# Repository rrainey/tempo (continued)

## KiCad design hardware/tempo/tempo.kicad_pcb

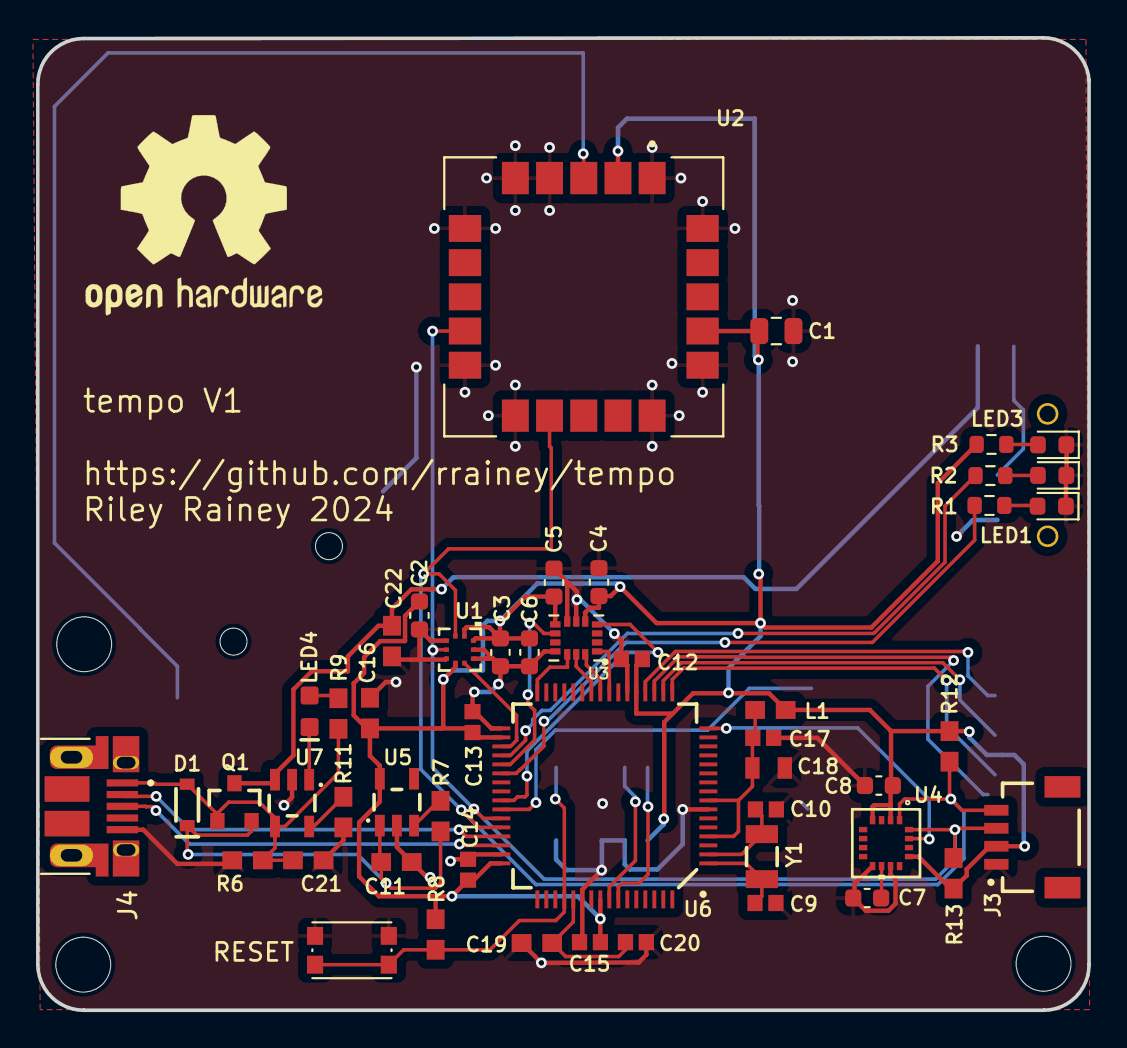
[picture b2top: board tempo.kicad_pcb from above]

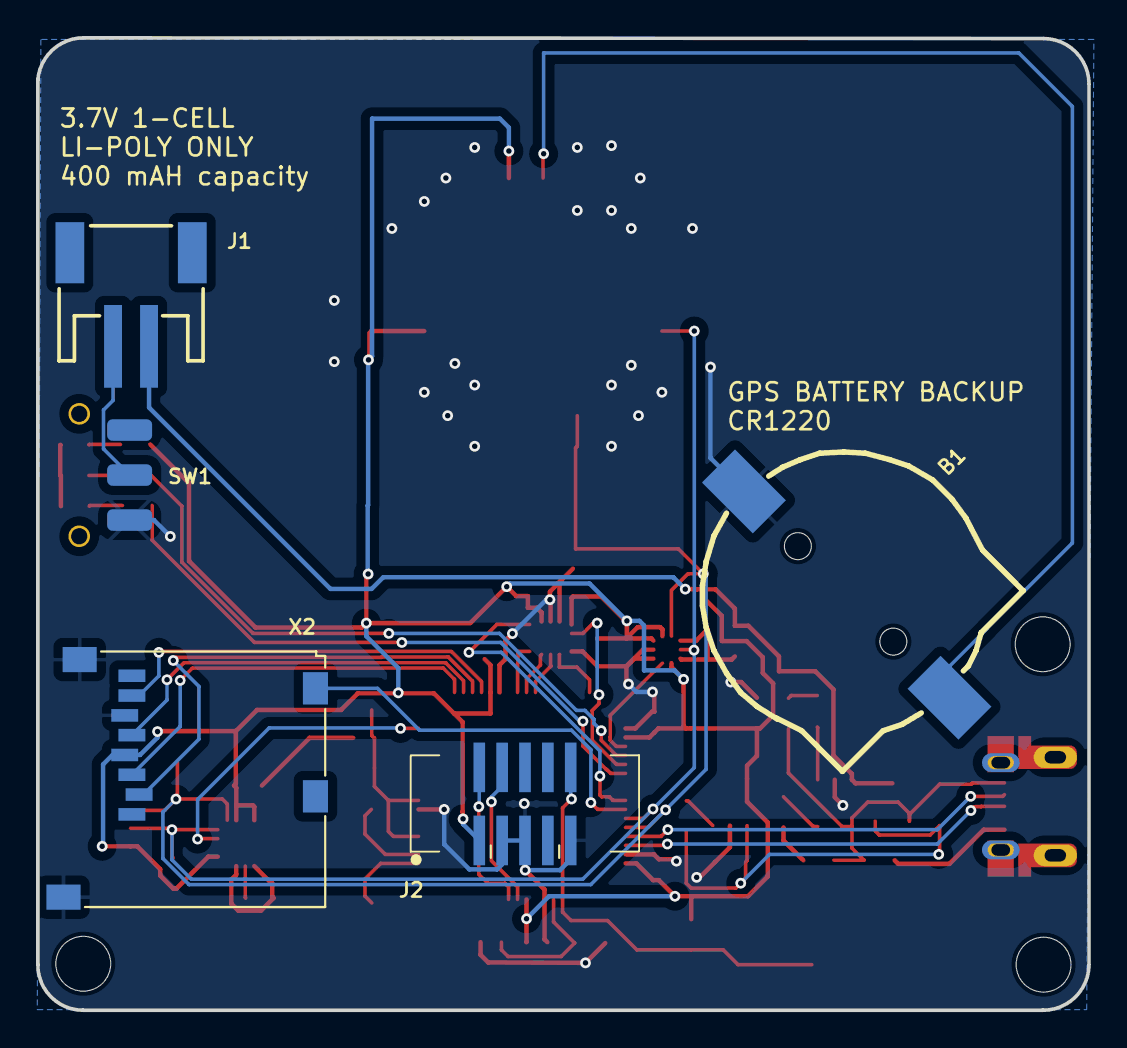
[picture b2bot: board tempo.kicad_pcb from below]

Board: 2 copper layers, 58.4 x 54.0 mm, 60 parts (5 on the bottom side), 41 nets.

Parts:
B1: CR1220; CR1220-2
C1: 10uF; C_0805_2012Metric
C2, C3: 100nF; C_0603_1608Metric
C4: 0.1uF; C_0603_1608Metric
C5: 10nF; C_0603_1608Metric
C6: 2.2uF; C_0603_1608Metric
C7, C8: 10uF; C_0603_1608Metric
C9, C10: 15PF-0402-50V-5%; 0402
C11: 1.0UF-0603-16V-10%-X7R; 0603
C12, C13, C14, C15, C17, C20: 0.1UF-0402-16V-10%; 0402
C16: 2.2UF-0603-10V-20%; 0603
C18: 10UF-0805-10V-10%; 0805
C19, C21, C22: 4.7UF-0603-6.3V-(10%); 0603
D1: 1A/23V/620mV; SOD-323
FRAME1: FRAME-LETTER; CREATIVE_COMMONS
H1, H2, H3: STAND-OFFTIGHT; STAND-OFF-TIGHT
J1: JSTPH; JSTPH2
J2: 3221-10-0300-00-TR
J3: QWIIC_CONNECTORJS-1MM; JST04_1MM_RA
J4: 10103594-0001LF; AMPHENOL_10103594-0001LF
L1: 220 Ω FERRITE; 0603
LED1, LED3: LTST-S270KGKT; LED_0603_1608Metric
LED2: LTST-S270KRKT; LED_0603_1608Metric
LED4: Yellow; LED-0603
LOGO2: OSHW-LOGOS; OSHW-Logo2_14.6x12mm_SilkScreen
Q1: DMP3125L; SOT23-3@1
R1, R2, R3: 2.2K; R_0603_1608Metric
R6, R7, R8: 10KOHM-0603-1/10W-1%; 0603
R9: 1K; 0603
R11: 2.0k; 0603
R12, R13: 2.2KOHM-0603-1/10W-1%; 0603
S1: RESET; SW_Push_1P1T_NO_CK_KMR2
SW1: JS102011SAQN
U1: BMP390; LGA10_BMP390_BOS
U2: SAM-M10Q; MODULE_SAM-M8Q-0-10
U3: ICM-42688-V; PQFN50P300X250X97-14N
U4: MMC5983MA; MMC5983MA_MEM
U5: SPX3819M5-L-3-3/TR; SOT23-5
U6: ATSAMD51J20A-A; TQFP64
U7: MCP73831; SOT23-5
X2: MEM2061-01-188-00-A; MICROSD
Y1: 32.768kHz; CRYSTAL-SMD-3.2X1.5MM

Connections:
3.3V: C1.1, C2.1, C3.1, C4.1, C5.1, C6.1, C8.1, C12.1, C13.1, C14.1, C15.1, C16.1, J2.1, J3.2, L1.1, R3.1, R8.2, R12.2, R13.2, U1.1 (VDDIO), U1.6 (CSB), U1.10 (VDD), U2.2 (VCC_IO), U2.17 (VCC), U3.5 (VDDIO), U3.8 (VDD), U4.2 (VDD), U4.4 (SPI_CS), U4.13 (VDDIO), U5.5 (OUT), U6.21 (VDDIO0), U6.34 (VDDIO1), U6.48 (VDDIO2), U6.56 (VDDIO3), X2.4 (SD_VDD)
/D5: U3.12 (AP_CS), U6.32 (PA15)
/D6: U3.4 (INT1/INT), U6.41 (PA20)
/D7: U6.42 (PA21), X2.CD1 (CARD_DETECT)
/D9: U4.15 (INT), U6.16 (PA07)
/D10: U3.9 (INT2/FSYNC/CLKIN), U6.37 (PA18)
/D11: U1.7 (INT), U6.35 (PA16)
/D12: R1.1, U6.38 (PA19)
/D13: R2.1, U6.36 (PA17)
/D+: J4.3 (D+), U6.46 (PA25)
/D-: J4.2 (D-), U6.45 (PA24)
/EN: R7.1, U5.3 (EN)
/FLASH_CS: U6.19 (PA10), X2.2 (CS)
/FLASH_MISO: U6.20 (PA11), X2.7 (DATA_OUT)
/FLASH_MOSI: U6.17 (PA08), X2.3 (DATA_IN)
/FLASH_SCK: U6.18 (PA09), X2.5 (SCLK)
/MISO: U3.1 (AP_SDO/AP_AD0), U6.24 (PB11)
/MOSI: U3.14 (AP_SDA/AP_SDIO/AP_SDI), U6.25 (PB12)
/SCK: U3.13 (AP_SCL/AP_SCLK), U6.26 (PB13)
/SCL: J3.4, R12.1, U1.2 (SCK), U2.12 (SCL), U4.1 (SCL/SPI_SCK), U6.44 (PA23)
/SDA: J3.3, R13.1, U1.4 (SDI), U2.9 (SDA), U4.16 (SDA/SPI_SDI), U6.43 (PA22)
/SWDCLK: J2.4, U6.57 (PA30)
/SWDIO: J2.2, U6.58 (PA31)
/VBACKUP: B1.+, U2.3 (V_BCKP)
/XIN32: C9.1, U6.1 (PA00), Y1.P$1 (1)
/XOUT32: C10.1, U6.2 (PA01), Y1.P$2 (2)
/~RESET: J2.10, R8.1, S1.2, U6.52 (~RESET)
GND: B1.-, C1.2, C2.2, C3.2, C4.2, C5.2, C6.2, C7.2, C8.2, C9.2, C10.2, C11.2, C12.2, C13.2, C14.2, C15.2, C16.2, C17.2, C18.2, C19.2, C20.2, C21.2, C22.2, J2.3, J2.5, J2.9, J3.1, J4.5 (GND), LED1.1 (K), LED2.1 (K), LED3.1 (K), R6.1, R11.1, S1.1, SW1.3 (C), U1.3 (VSS), U1.5 (SDO), U1.8 (VSS), U1.9 (VSS), U2.1 (GND), U2.4 (GND), U2.5 (GND), U2.6 (GND), U2.10 (GND), U2.11 (GND), U2.15 (GND), U2.16 (GND), U2.20 (GND), U3.6 (GND), U3.7 (RESV_7), U3.11 (RESV_11), U4.9 (GND), U4.11 (GND), U5.2 (GND), U6.7 (GND0), U6.22 (GND1), U6.33 (GND2), U6.47 (GND3), U6.54 (GND4), U7.2 (VSS), X2.6 (GND@3), X2.MT1 (GND@2), X2.MT2 (GND@1)
unnamed: LED1.2 (A), R1.2
unnamed: LED2.2 (A), R2.2
unnamed: LED3.2 (A), R3.2
unnamed: LED4.A, R9.2
unnamed: J1.1, SW1.2 (B)
unnamed: C7.1, U4.10 (CAP)
unnamed: R11.2, U7.5 (PROG)
unnamed: LED4.C, U7.1 (STAT)
VCC: C19.1, C20.1, U6.53 (VDDCORE)
VDDA: C17.1, C18.1, L1.2, U6.4 (PA03), U6.8 (VDDANA)
VIN: C11.1, D1.C, Q1.2 (S), R7.2, U5.1 (IN)
V_BATT: C22.1, J1.2, Q1.3 (D), U7.3 (VBAT)
V_USB: C21.1, D1.A, J4.1 (VCC), Q1.1 (G), R6.2, R9.1, U7.4 (VIN)

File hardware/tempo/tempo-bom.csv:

Source:,C:\Users\rrain\OneDrive\Documents\GitHub\SAMD51_Thing_Plus\peakick\peakick.kicad_sch,,,,,,,,,,,,,,
Date:,2/8/2024 16:50,,,,,,,,,,,,,,
Tool:,Eeschema 7.0.5,,,,,,,,,,,,,,
Generator:,C:\Program Files\KiCad\7.0\bin\scripting\plugins/bom_csv_grouped_by_value.py,,,,,,,,,,,,,,
Component Count:,55,,,,,,,,,,,,,,
,,,,,,,,,,,,,,,
Collated Components:,,,,,,,,,,,,,,,
,,,,,,,,,,,,,,,
Item,Qty,Reference(s),Value,LibPart,Footprint,Datasheet,DNP,MANUFACTURER,MAXIMUM_PACKAGE_HEIGHT,MPN,NOTES,PACKAGE,PARTREV,PROD_ID,STANDARD
1,1,B1,CR1220,peakick:BATTERYCR1220_2,peakick:CR1220-2,https://www.keyelco.com/userAssets/file/M65p2.pdf,,Keystone,,1056TR,BATT HOLDER,,,,
2,1,C1,10uF,Device:C,Capacitor_SMD:C_0805_2012Metric,~,,,,,,0805,,,
3,2,"C2, C3",100nF,Device:C_Small,Capacitor_SMD:C_0603_1608Metric,~,,,,,X7R,0603,,,
4,1,C4,0.1uF,Device:C_Small,Capacitor_SMD:C_0603_1608Metric,~,,,,,X7R,0603,,,
5,1,C5,10nF,Device:C_Small,Capacitor_SMD:C_0603_1608Metric,~,,,,,X7R,0603,,,
6,1,C6,2.2uF,Device:C_Small,Capacitor_SMD:C_0603_1608Metric,~,,,,,X7R,0603,,,
7,2,"C7, C8",10uF,Device:C_Small,Capacitor_SMD:C_0603_1608Metric,~,,,,,X7R,0603,,,
8,2,"C9, C10",15PF-0402-50V-5%,SAMD51_Thing_Plus-eagle-import:15PF-0402-50V-5%,0402,,,,,,,0402,,,
9,1,C11,1.0UF-0603-16V-10%-X7R,SAMD51_Thing_Plus-eagle-import:1.0UF-0603-16V-10%-X7R,0603,,,,,,,0603,,,
10,6,"C12, C13, C14, C15, C17, C20",0.1UF-0402-16V-10%,SAMD51_Thing_Plus-eagle-import:0.1UF-0402-16V-10%,0402,,,,,,,0402,,,
11,1,C16,2.2UF-0603-10V-20%,SAMD51_Thing_Plus-eagle-import:2.2UF-0603-10V-20%,0603,,,,,,,0603,,,
12,1,C18,10UF-0805-10V-10%,SAMD51_Thing_Plus-eagle-import:10UF-0805-10V-10%,0805,,,,,,,0805,,,
13,3,"C19, C21, C22",4.7UF-0603-6.3V-(10%),SAMD51_Thing_Plus-eagle-import:4.7UF-0603-6.3V-(10%),0603,,,,,,,0603,,,
14,1,D1,1A/23V/620mV,SAMD51_Thing_Plus-eagle-import:DIODE-SCHOTTKY-BAT20J,SOD-323,,,,,,,SOD-323,,,
15,1,J1,JSTPH,Adafruit Feather M0 Adalogger-eagle-import:CON_JST_PH_2PIN,JSTPH2,,,JST,5.5mm,S2B-PH-SM4-TB,,,,,
16,1,J2,3221-10-0300-00-TR,20021221:20021221-00010C4LF,peakick:3221-10-0300-00-TR,https://media.digikey.com/pdf/Data%20Sheets/CNC%20Tech%20PDF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,,,,3221-10-0300-00-TR,,,,,
17,1,J3,QWIIC_CONNECTORJS-1MM,SAMD51_Thing_Plus-eagle-import:QWIIC_CONNECTORJS-1MM,JST04_1MM_RA,,DNP,JST,,SM04B-SRSS-TB,do not place,,,,
18,1,J4,AMP FCI 10103594-0001LF,SAMD51_Thing_Plus-eagle-import:USB_MICRO-B_HALF_PTH_MILL,USB-MICROB-PTH-MILL,,,,,,,,,,
19,1,L1,220 Ω FERRITE,SAMD51_Thing_Plus-eagle-import:INDUCTORFB-30OHM,0603,,,MURATA,,BLM18RK221SN1D,see DS60001507E-page 2098,,,NDUC-07859,
20,2,"LED1, LED3",LTST-S270KGKT,Device:LED,LED_SMD:LED_0603_1608Metric,~,,Lite-On,,LTST-S270KGKT,GREEN LED,,,,
21,1,LED2,LTST-S270KRKT,Device:LED,LED_SMD:LED_0603_1608Metric,~,,Lite-On,,LTST-S270KRKT,RED LED,,,,
22,1,LED4,Yellow,SAMD51_Thing_Plus-eagle-import:LED-YELLOW0603,LED-0603,,,Lite-On,,LTST-S270YKT,YELLOW LED,,,,
23,1,Q1,DMP3125L,SAMD51_Thing_Plus-eagle-import:MOSFET-PCHANNELDMG2307L,SOT23-3@1,https://www.diodes.com/assets/Datasheets/DMP3125L.pdf,,Diodes Incorporated,,DMP3125L,DMP3125L or DMG2307L,SOT23,,,
24,3,"R1, R2, R3",2.2K,Adafruit MPU6050-eagle-import:RESISTOR_0603_NOOUT,Resistor_SMD:R_0603_1608Metric,,,,,,10%,0603,,,
25,3,"R6, R7, R8",10KOHM-0603-1/10W-1%,SAMD51_Thing_Plus-eagle-import:10KOHM-0603-1/10W-1%,0603,,,,,,,0603,,,
26,1,R9,1K,SAMD51_Thing_Plus-eagle-import:1KOHM-1/10W-1%(0603),0603,,,,,,,0603,,,
27,1,R11,2.0k,SAMD51_Thing_Plus-eagle-import:2.0KOHM1/10W5%(0603),0603,,,,,,,0603,,,
28,2,"R12, R13",2.2KOHM-0603-1/10W-1%,SAMD51_Thing_Plus-eagle-import:2.2KOHM-0603-1/10W-1%,0603,,,,,,,0603,,,
29,1,S1,RESET,peakick:KMR2_TACTILE_SWITCH,Button_Switch_SMD:SW_Push_1P1T_NO_CK_KMR2,https://www.ckswitches.com/media/1479/kmr2.pdf,,CK Switches,,KMR221 LFS,,,,,
30,1,SW1,JS102011SAQN,Switch:SW_SPDT,peakick:JS102011SAQN,https://www.ckswitches.com/media/1422/js.pdf,,CK Switches,,JS102011SAQN,,,,,
31,1,U1,BMP390,peakick:BMP390,LGA10_BMP390_BOS,BMP390,,Bosch Sensortec,,BMP390,,LGA-10,,,
32,1,U2,SAM-M10Q,dropkick:SAM-M8Q-0-10,MODULE_SAM-M8Q-0-10,https://content.u-blox.com/sites/default/files/documents/SAM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,,u-blox,6.80mm,SAM-M10Q-00B,GNSS RECEIVER,,R07,,Manufacturer Recommendations
33,1,U3,ICM-42688-V,dropkick:ICM-42688-P,peakick:PQFN50P300X250X97-14N,,,TDK InvenSense,0.97mm,ICM-42688-V,,LGA-14,1.2,,IPC-7351B
34,1,U4,MMC5983MA,peakick:MMC5983MA,MMC5983MA_MEM,https://www.mouser.com/datasheet/2/821/Memsic_09102019_MMC59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,,,1.0mm,MMC5983MA,,LGA-16,,,
35,1,U5,SPX3819M5-L-3-3/TR,SAMD51_Thing_Plus-eagle-import:V_REG_LDOSMD,SOT23-5,,,Maxlinear,,SPX3819M5-L-3-3/TR,,,,VREG-12457,
36,1,U6,ATSAMD51J20A-A,SAMD51_Thing_Plus-eagle-import:ATSAMD51J20A-A,TQFP64,,,Microchip,,ATSAMD51J20A-AUT,,,,,
37,1,U7,MCP73831,SAMD51_Thing_Plus-eagle-import:MCP73831,SOT23-5,,,Microchip,,MCP73831T-4ADI/OT,,,,,
38,1,X2,MEM2061-01-188-00-A,Adafruit Feather M0 Adalogger-eagle-import:MICROSD,MICROSD,https://gct.co/files/specs/mem2061-spec.pdf,,GCT,,MEM2061-01-188-00-A,,,,,
39,1,Y1,32.768kHz,SAMD51_Thing_Plus-eagle-import:CRYSTAL-32.768KHZSMD-3.2X1.5,CRYSTAL-SMD-3.2X1.5MM,https://www.mouser.com/datasheet/2/137/FC_255_en-1649561.pdf,,SEIKO EPSON,,FC-135 32.7680KA-A5,,,,,

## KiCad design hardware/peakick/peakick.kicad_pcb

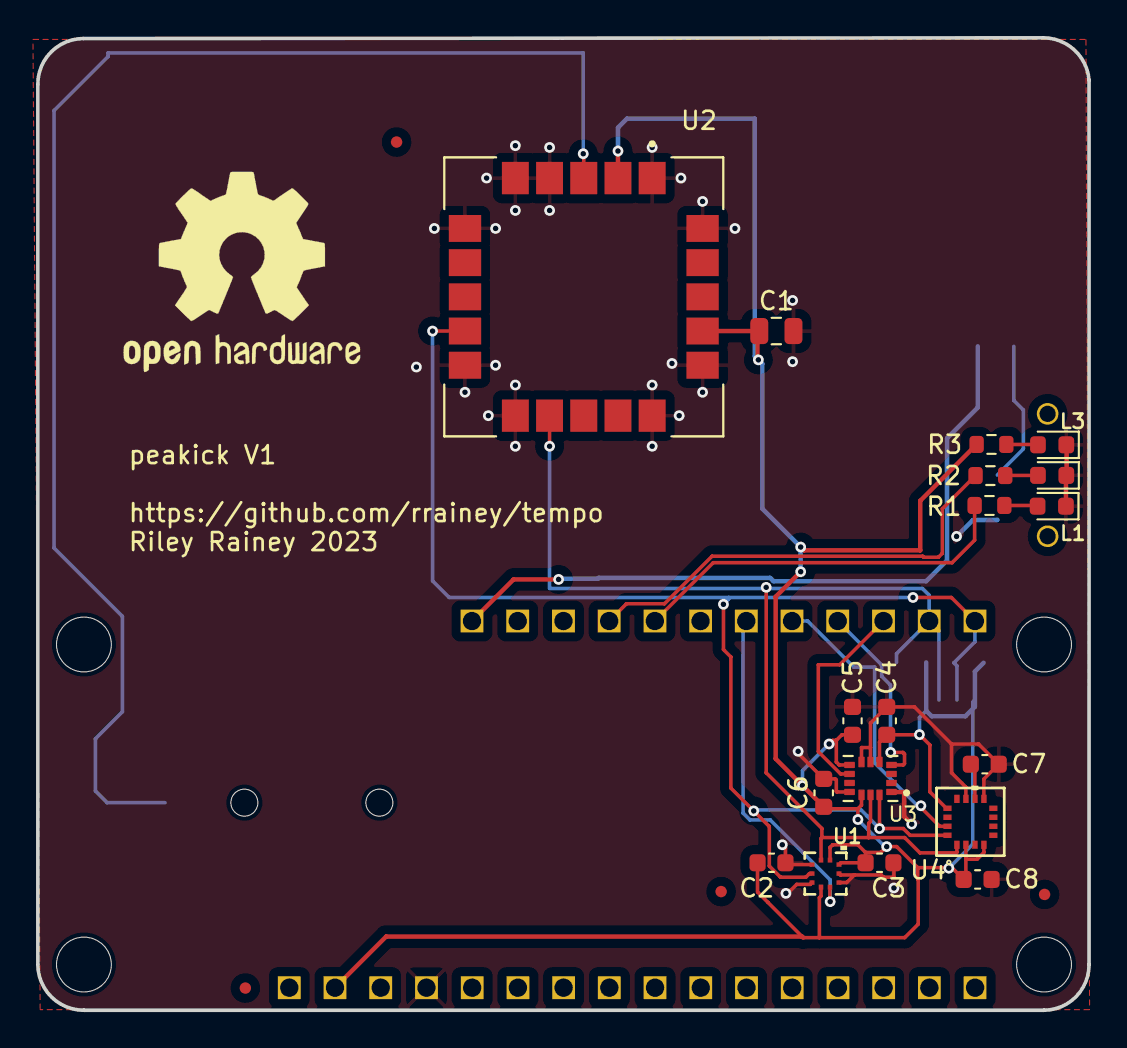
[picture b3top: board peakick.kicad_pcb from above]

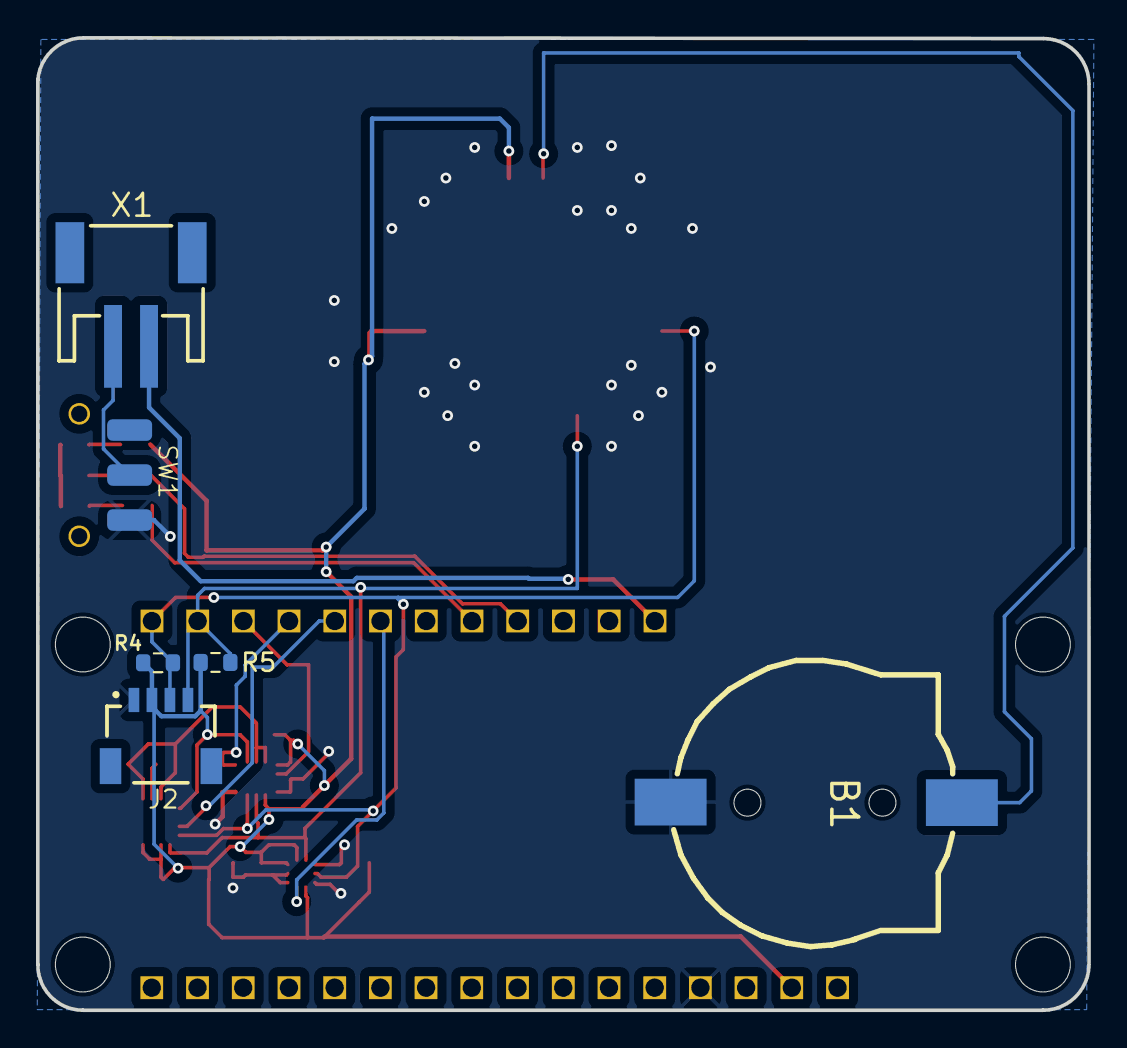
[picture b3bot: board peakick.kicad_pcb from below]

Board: 2 copper layers, 58.4 x 54.0 mm, 36 parts (6 on the bottom side), 17 nets.

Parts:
B1: CR1220; CR1220-2
C1: 10uF; C_0805_2012Metric
C2, C3: 100nF; C_0603_1608Metric
C4: 0.1uF; C_0603_1608Metric
C5: 10nF; C_0603_1608Metric
C6: 2.2uF; C_0603_1608Metric
C7, C8: 10uF; C_0603_1608Metric
FD1, FD2, FD3, FD4: FIDUCIALUFIDUCIAL; FIDUCIAL-MICRO
FRAME1: FRAME-LETTER; CREATIVE_COMMONS
H1, H2, H3, H4: STAND-OFFTIGHT; STAND-OFF-TIGHT
J1: CONN_161X16_SM_SQ_NOSILK; 1X16_SM_SQ_NOSILK
J2: QWIIC_RA; JST04_1MM_RA
J3: CONN_12SM_SQ_NO_SILK; 1X12_SM_SQ_NOSILK
L1, L3: LTST-S270KGKT; LED_0603_1608Metric
L2: LTST-S270KRKT; LED_0603_1608Metric
LOGO2: OSHW-LOGOS; OSHW-Logo2_14.6x12mm_SilkScreen
R1, R2, R3: 2.2K; R_0603_1608Metric
R4, R5: DNP; R_0603_1608Metric
SW1: JS102011SAQN
U1: BMP390; LGA10_BMP390_BOS
U2: SAM-M10Q; MODULE_SAM-M8Q-0-10
U3: ICM-42688-P; PQFN50P300X250X97-14N
U4: MMC5983MA; MMC5983MA_MEM
X1: JSTPH; JSTPH2

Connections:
3.3V: C1.1, C2.1, C3.1, C4.1, C5.1, C6.1, C8.1, J1.15, J2.2, R3.1, R4.1, R5.1, U1.1 (VDDIO), U1.6 (CSB), U1.10 (VDD), U2.2 (VCC_IO), U2.17 (VCC), U3.5 (VDDIO), U3.8 (VDD), U3.12 (AP_CS), U4.2 (VDD), U4.4 (SPI_CS), U4.13 (VDDIO)
/D4: J3.3, U3.9 (INT2/FSYNC/CLKIN)
/D6: J3.4, U3.4 (INT1/INT)
/D8: J3.5, U4.15 (INT)
/D10: J3.6, U1.7 (INT)
/D12: J3.8, R1.1
/D13: J3.9, R2.1
/SCL: J2.4, J3.2, R5.2, U1.2 (SCK), U2.12 (SCL), U3.13 (AP_SCL/AP_SCLK), U4.1 (SCL/SPI_SCK)
/SDA: J2.3, J3.1, R4.2, U1.4 (SDI), U2.9 (SDA), U3.14 (AP_SDA/AP_SDIO/AP_SDI), U4.16 (SDA/SPI_SDI)
/VBACKUP: B1.+, U2.3 (V_BCKP)
GND: B1.-, C1.2, C2.2, C3.2, C4.2, C5.2, C6.2, C7.2, C8.2, J1.13, J2.1, L1.1 (K), L2.1 (K), L3.1 (K), SW1.3 (C), U1.3 (VSS), U1.5 (SDO), U1.8 (VSS), U1.9 (VSS), U2.1 (GND), U2.4 (GND), U2.5 (GND), U2.6 (GND), U2.10 (GND), U2.11 (GND), U2.15 (GND), U2.16 (GND), U2.20 (GND), U3.1 (AP_SDO/AP_AD0), U3.6 (GND), U3.7 (RESV_7), U3.11 (RESV_11), U4.9 (GND), U4.11 (GND)
unnamed: L1.2 (A), R1.2
unnamed: L2.2 (A), R2.2
unnamed: L3.2 (A), R3.2
unnamed: SW1.2 (B), X1.1
unnamed: C7.1, U4.10 (CAP)
V_BATT: J3.12, X1.2

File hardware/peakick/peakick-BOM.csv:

"Source:","C:\Users\rrain\OneDrive\Documents\GitHub\tempo\hardware\peakick\peakick.kicad_sch"
"Date:","12/18/2023 11:48:49 AM"
"Tool:","Eeschema 7.0.5"
"Generator:","C:\Program Files\KiCad\7.0\bin\scripting\plugins/bom_csv_grouped_by_value.py"
"Component Count:","26"

"Collated Components:"

"Item","Qty","Reference(s)","Value","LibPart","Footprint","Datasheet","DNP","MANUFACTURER","MAXIMUM_PACKAGE_HEIGHT","MPN","Manufacturer Part","NOTES","PACKAGE","PARTREV","STANDARD"
"1","1","B1","CR1220","peakick:BATTERYCR1220_2","peakick:CR1220-2","https://www.keyelco.com/userAssets/file/M65p2.pdf","","Keystone","","1056TR","","BATT HOLDER","","",""
"2","1","C1","10uF","Device:C","Capacitor_SMD:C_0805_2012Metric","~","","","","","","","0805","",""
"3","2","C2, C3","100nF","Device:C_Small","Capacitor_SMD:C_0603_1608Metric","~","","","","","","X7R","0603","",""
"4","1","C4","0.1uF","Device:C_Small","Capacitor_SMD:C_0603_1608Metric","~","","","","","","X7R","0603","",""
"5","1","C5","10nF","Device:C_Small","Capacitor_SMD:C_0603_1608Metric","~","","","","","","X7R","0603","",""
"6","1","C6","2.2uF","Device:C_Small","Capacitor_SMD:C_0603_1608Metric","~","","","","","","X7R","0603","",""
"7","2","C7, C8","10uF","Device:C_Small","Capacitor_SMD:C_0603_1608Metric","~","","","","","","X7R","0603","",""
"8","1","J1","CONN_161X16_SM_SQ_NOSILK","peakick:CONN_161X16_SM_SQ_NOSILK","peakick:1X16_SM_SQ_NOSILK","","DNP","","","","","DNP","","",""
"9","1","J2","QWIIC_RA","peakick:QWIIC_CONNECTORJS-1MM","peakick:JST04_1MM_RA","","DNP","","","","","DNP","","",""
"10","1","J3","CONN_12SM_SQ_NO_SILK","peakick:CONN_12SM_SQ_NO_SILK","peakick:1X12_SM_SQ_NOSILK","","DNP","","","","","DNP","","",""
"11","2","L1, L3","LTST-S270KGKT","Device:LED","LED_SMD:LED_0603_1608Metric","~","","Lite-On","","LTST-S270KGKT","","GREEN LED","","",""
"12","1","L2","LTST-S270KRKT","Device:LED","LED_SMD:LED_0603_1608Metric","~","","Lite-On","","LTST-S270KRKT","","RED LED","","",""
"13","3","R1, R2, R3","2.2K","Adafruit MPU6050-eagle-import:RESISTOR_0603_NOOUT","Resistor_SMD:R_0603_1608Metric","","","","","","","10%","0603","",""
"14","2","R4, R5","DNP","Device:R","Resistor_SMD:R_0603_1608Metric","~","DNP","","","","","10K if SAM-M10 not installed","0603","",""
"15","1","SW1","JS102011SAQN","Switch:SW_SPDT","peakick:JS102011SAQN","https://www.ckswitches.com/media/1422/js.pdf","","CK Switches","","JS102011SAQN","","","","",""
"16","1","U1","BMP390","peakick:BMP390","LGA10_BMP390_BOS","BMP390","","Bosch Sensortec","","BMP390","","","LGA-10","",""
"17","1","U2","SAM-M10Q","dropkick:SAM-M8Q-0-10","MODULE_SAM-M8Q-0-10","https://content.u-blox.com/sites/default/files/documents/SAM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","","u-blox","6.80mm","SAM-M10Q-00B","","GNSS RECEIVER","","R07","Manufacturer Recommendations"
"18","1","U3","ICM-42688-P","dropkick:ICM-42688-P","peakick:PQFN50P300X250X97-14N","","","TDK InvenSense","0.97mm","ICM-42688-P","","","LGA-14","1.2","IPC-7351B"
"19","1","U4","MMC5983MA","peakick:MMC5983MA","MMC5983MA_MEM","https://www.mouser.com/datasheet/2/821/Memsic_09102019_MMC59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","","","1.0mm","MMC5983MA","","","LGA-16","",""
"20","1","X1","JSTPH","Adafruit Feather M0 Adalogger-eagle-import:CON_JST_PH_2PIN","JSTPH2","","","JST","5.5mm","S2B-PH-SM4-TB","S2B-PH-SM4-TB","","","",""

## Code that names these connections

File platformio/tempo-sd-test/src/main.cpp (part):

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
/*
static const uint8_t FLASH_SS	= 34 ;	// SERCOM0 last PAD is present on 34 but HW SS isn't used. Set here only for reference.
static const uint8_t FLASH_MOSI = PIN_SPI1_MOSI ;
static const uint8_t FLASH_MISO = PIN_SPI1_MISO ;
static const uint8_t FLASH_SCK  = PIN_SPI1_SCK ;
*/

/*
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
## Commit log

2023-10-15 Initial import
2023-10-15 Add image and list of sensors
2023-10-31 Doc updates
2023-10-31 typo
2023-12-18 Add Gerber, tweak BOM, remove solder mask around IMU pads
2024-01-15 Initial tempo firmware - untested
2024-01-15 tidying
2024-01-16 Initial testing passes
2024-01-23 initial commit of driver test code
2024-01-24 image for assembly instructions
2024-02-02 driver_tests sketch updates for better FIFO performance
2024-02-02 Add pull-ups for I2C
2024-02-02 add extra attribution comments
2024-02-10 staging partial updates for V1 tempo design
2024-02-10 tempo V1 PCB commit
2024-02-13 Important fix to ICM42688 driver FIFO handling; add fusion_tests sketch
2024-02-13 renamed new tempo project
2024-02-17 updates to ICM driver and renewed testing with ESP32
2024-05-30 SD card test and raw sensor data logger pio projects
2024-05-31 error handling enhancements
2024-06-01 clean up subdirectory creation
2024-10-30 interim commit of logger application code
2024-10-31 fix compile issues
2024-10-31 repair code copied from dropkick
2024-10-31 test SD card performance by logging all raw sansor data to a binary file
2024-10-31 ignore .pio folders
2024-10-31 experimental Ardiuno test of Fusion library
2024-10-31 platformio version of Fusion library tests
2024-10-31 sensor calibration tests
2024-10-31 updated pcb and enclosure files
2024-10-31 add initial hardware and software files for tempo project
2024-10-31 ignore Python and pio tmp files
2024-10-31 compiles but still needs Fusion module integrated
2024-10-31 update a comment
2024-10-31 Add rudimentary AHRS processing
2024-10-31 add TODO comment about passing high res timestamps
2024-10-31 Add TXT log flushing
2024-10-31 improve handling of initialzation error indicator LEDs
2024-10-31 pass IMU interrupt timestamp along with IMU samples
2024-10-31 change size of IMU thimestamp queue to align with maximum FIFO storage
2024-10-31 Fix warning on handleIMUSample potentiall passing an initialized value
2024-11-01 Add TXT logging
2024-11-02 Tighter implementation of the Morse blinker
2024-11-02 Clearer state control (and initialization)
2024-11-02 added debugging
2024-11-02 include message when in test mode
2024-11-02 fix LED state indication
2024-11-02 altitude sampling wasn't in the main loop
2024-11-02 add documentation comments
2024-11-02 Document error codes
2024-11-02 Updated introduction
2024-11-02 Repaired an issue withfinding and allocating new log file slots.
2024-11-02 repair a few issues in the app state management
2024-11-02 Improved a couple of information messages.
2024-11-02 fix SdFat directory traversal problem
2024-11-02 truncate TXT log files before closing
2024-11-02 continue breaking out functions in the app state management
2024-11-03 fine tune blink states; close binary log when returning to WAIT
2024-11-03 Add a rudimentary initial version of a desktop visualizer app
2024-11-03 add graphic depicting axes for each sensor
2024-11-03 output quaternion orientation state so that we can integrate with "visualizer" desktop app
2024-11-04 Add WaveFront object representing Tempo with enclosure. Render it
2024-11-04 Update installtion instructions
2024-11-04 Updated installation instruction
2024-11-04 Write IMU raw data to binary log file.
2024-11-04 Update code to bring it a bit more in line with the final versions that were used in the temp-logger app.
2024-11-05 visuals match hand rotations
2024-11-05 Convert sensor frames to body frame before handing to AHRS
2024-11-05 use sensor frame for Fusion gyro correction filter
2024-11-05 incomplete merge of fusion_tests changes
2024-11-05 Add Help panel
2024-11-09 Added conditional code to print IMU interrupt counts
2024-11-09 Add plot of magnetic strength vector
2024-11-11 Incomplete changes to explore adding dropkick support to this project
2024-11-11 Small updates to information and error messages
2024-11-12 Add ArduinoJson to prepare for SD base configuration files
2024-11-12 Fix issue with log file slot number search
2024-11-12 Add version 156 of file format (logging state changes); add capability to only log the TXT file.
2024-11-12 $PIMU values were not being taken from the best source. $PIMU/$PIM2 timestamps now match
2024-11-12 Make the build type production ready by making the default mode "FLIGHT_MODE"
2024-11-13 Started some experimentation with using this code with Dropkick boards. Not fully ready.
2024-11-14 Minor doc updates
2024-11-14 Fix misc typos
2024-11-30 PTH record timestamp was incorrectly showing absolute millis() rather than an offset relative to start of logfile.
2024-12-07 Use of bad dtostrf() implementation was causing havoc in the AHRS readout.
2024-12-09 First stable version of this visualizer application.
2024-12-09 attribution for the human model
2025-01-05 Early working version validated against a live log file
2025-01-06 Add a simple NMEA-0183 summarizer. Built by Grok.
2025-01-06 Updated version with basic scrubbing functionality.
2025-01-07 Comment refinement
2025-01-11 Update instructions and port
2025-01-11 ignore python virtual environment artifacts
2025-01-20 Upgrade to KiCad 8.0 and save V1 board gerbers
2025-02-19 Tempo-BT V1
2025-02-26 Add tempo-bt board fix reference image
2025-08-05 Updated enclosure
2025-08-10 Switch orientation incorrect; fixed
2025-08-17 Add V1 hardware documentation
2025-08-18 Through Task 5
2025-08-18 Through task 6
2025-08-18 Through task 8
2025-08-18 through task 10
2025-08-18 Through task 12
2025-08-18 Through task 13
2025-08-18 Through task 14
2025-08-18 Pase 4 complete.
2025-08-19 First BMP390 tests
2025-08-19 Working baseline for all devices except IMU and that may be a PCB issue
2025-08-20 Clean up device overlay and near-fix for BMP390 calibrated calculations.
2025-08-20 BMP390 calculations now functional. Follows Zephyr BMP388 driver
2025-08-22 New log file format; aggregator and testing
2025-08-22 Updates after stand alone IMU/Zephyr testing
2025-08-28 First full radio build
2025-08-29 File system tweaks. Improved SD Card Detect.
2025-08-31 Verify SD Card connects. BT fixes - now connects to nrf Connect. Add RGB LED driver, but needs more work.
2025-08-31 Update architecture document to reflect current status
2025-08-31 Add more direct reference to mcumgr
2025-09-04 led fixes
2025-09-05 IMU testing - add Madgewick orientation tracking
2025-09-06 Update NV memory settings for operational use.
2025-09-07 Phase 0 complete
2025-09-07 Through Task 9 - App layout
2025-09-07 Through task 19
2025-09-07 Through Phase 3.
2025-09-07 Phase 4 Complete.
2025-09-07 Through task 38
2025-09-07 Through Task 41.
2025-09-07 Phase 5 and 6 Complete.
2025-09-08 Through Phase 7 (task 53)
2025-09-08 Through Task 54.
2025-09-10 Basic setup instructions
2025-09-10 Task 56
2025-09-10 Try/catch not complete.
2025-09-10 Advertise as mock device for app testing
2025-09-11 Add remote LED blink control
2025-09-12 Numerous fixes and reconfiguration for first flight tests
2025-09-14 Numerous fixes; mapped app_state to logging_state
2025-09-14 Multiple updates
2025-09-14 Updates to smpmgr operations
2025-09-14 Through task 55
2025-09-14 add session-delete mcumgr function
2025-09-14 Log file extension should be TXT, not CSV
2025-09-14 add sample (experimentally) converted log file
2025-09-14 Throgh task 61.
2025-09-14 Through task 62: ensure idempotency of log storage.
2025-09-14 Through task 65.
2025-09-14 Through task 74 and Phase 9, "Analysis Worker"
2025-09-14 Through task 80 and Phase 10, "Home Panels & Jump Details"
2025-09-14 small add
2025-09-16 Some fixes an setting up for phase 11, "Formation Review"
2025-09-16 Add column for calibration factor
2025-09-17 First pass of Dropzones - preparing for Phase 11
2025-09-17 Through task 83
2025-09-17 Through task 85
2025-09-17 Phase 11 code complete but needs testing.
2025-09-17 The Quick Links section was redundant - removed
2025-09-17 Update architecture document
2025-09-18 Through Phase 12 - "Lending & Proxy Users"
2025-09-19 Testing fixes.
2025-09-21 Use live log data
2025-09-21 Switch to Supabse Storage for jump logs
2025-09-21 Improved event detection
2025-09-21 load formation
2025-09-21 Formation loading switched to Supabase Storage for logs
2025-09-21 Update App layout and fix to load formation into review page
2025-09-21 Trim log data to 15 seconds before jump.
2025-09-23 Add home DZ and next jump number; add first pass at fall rate analysis
2025-09-23 Add Timezone dropdown
2025-09-24 Documenmtation updates
2025-09-24 Add ability to manually import a log file
2025-09-24 Allow user to verify date and time before submission on manual log import.
2025-09-25 We were not displaying the jump date on jump summary and details.
2025-09-25 Fix possible null exit time.
2025-09-26 Add rounded bar chart
2025-09-26 Detail Phase 13 plan
2025-09-26 Through task 96
2025-09-26 Through task 97
2025-09-26 through Phase 13 - minus custom mcumgr command to initialize NVM
2025-09-27 Fully implement device initialization.
2025-09-27 Device name now taken from NVM settings.
2025-10-01 Clean up production build.
2025-10-06 Version 157 - fix loag-at-start issue; increase baro IIR filter
2025-10-07 Update phase 15
2025-10-07 Phase 15 — Visibility & Permissions Hardening + User connections
2025-10-08 Through Task 101
2025-10-08 Through task 102 - calibrated fall rate comparisons
2025-10-08 Tweak velocity bin chart.
2025-10-09 through task 106, data export.
2025-10-09 Through Task 107 - Delete Jump
2025-10-09 Fix issue with VelocityBinResponse handling.
2025-10-09 Task 108, delete invitations.
2025-10-09 Task 109: Delete Group with Promotion of new admin
2025-10-09 Minor color tweaks
2025-10-09 .env sample
2025-10-09 Docker MVP plan
2025-10-09 Fix lint issues
2025-10-10 Through Docker Pase D - task 139
2025-10-11 Phase F : Docker Compose
2025-10-11 Update .gitignore to avoid supabase/docker artifacts
2025-10-11 storage documentation
2025-10-11 Control and build scripts.
2025-10-11 Through task 171
2025-10-11 System documentation.
